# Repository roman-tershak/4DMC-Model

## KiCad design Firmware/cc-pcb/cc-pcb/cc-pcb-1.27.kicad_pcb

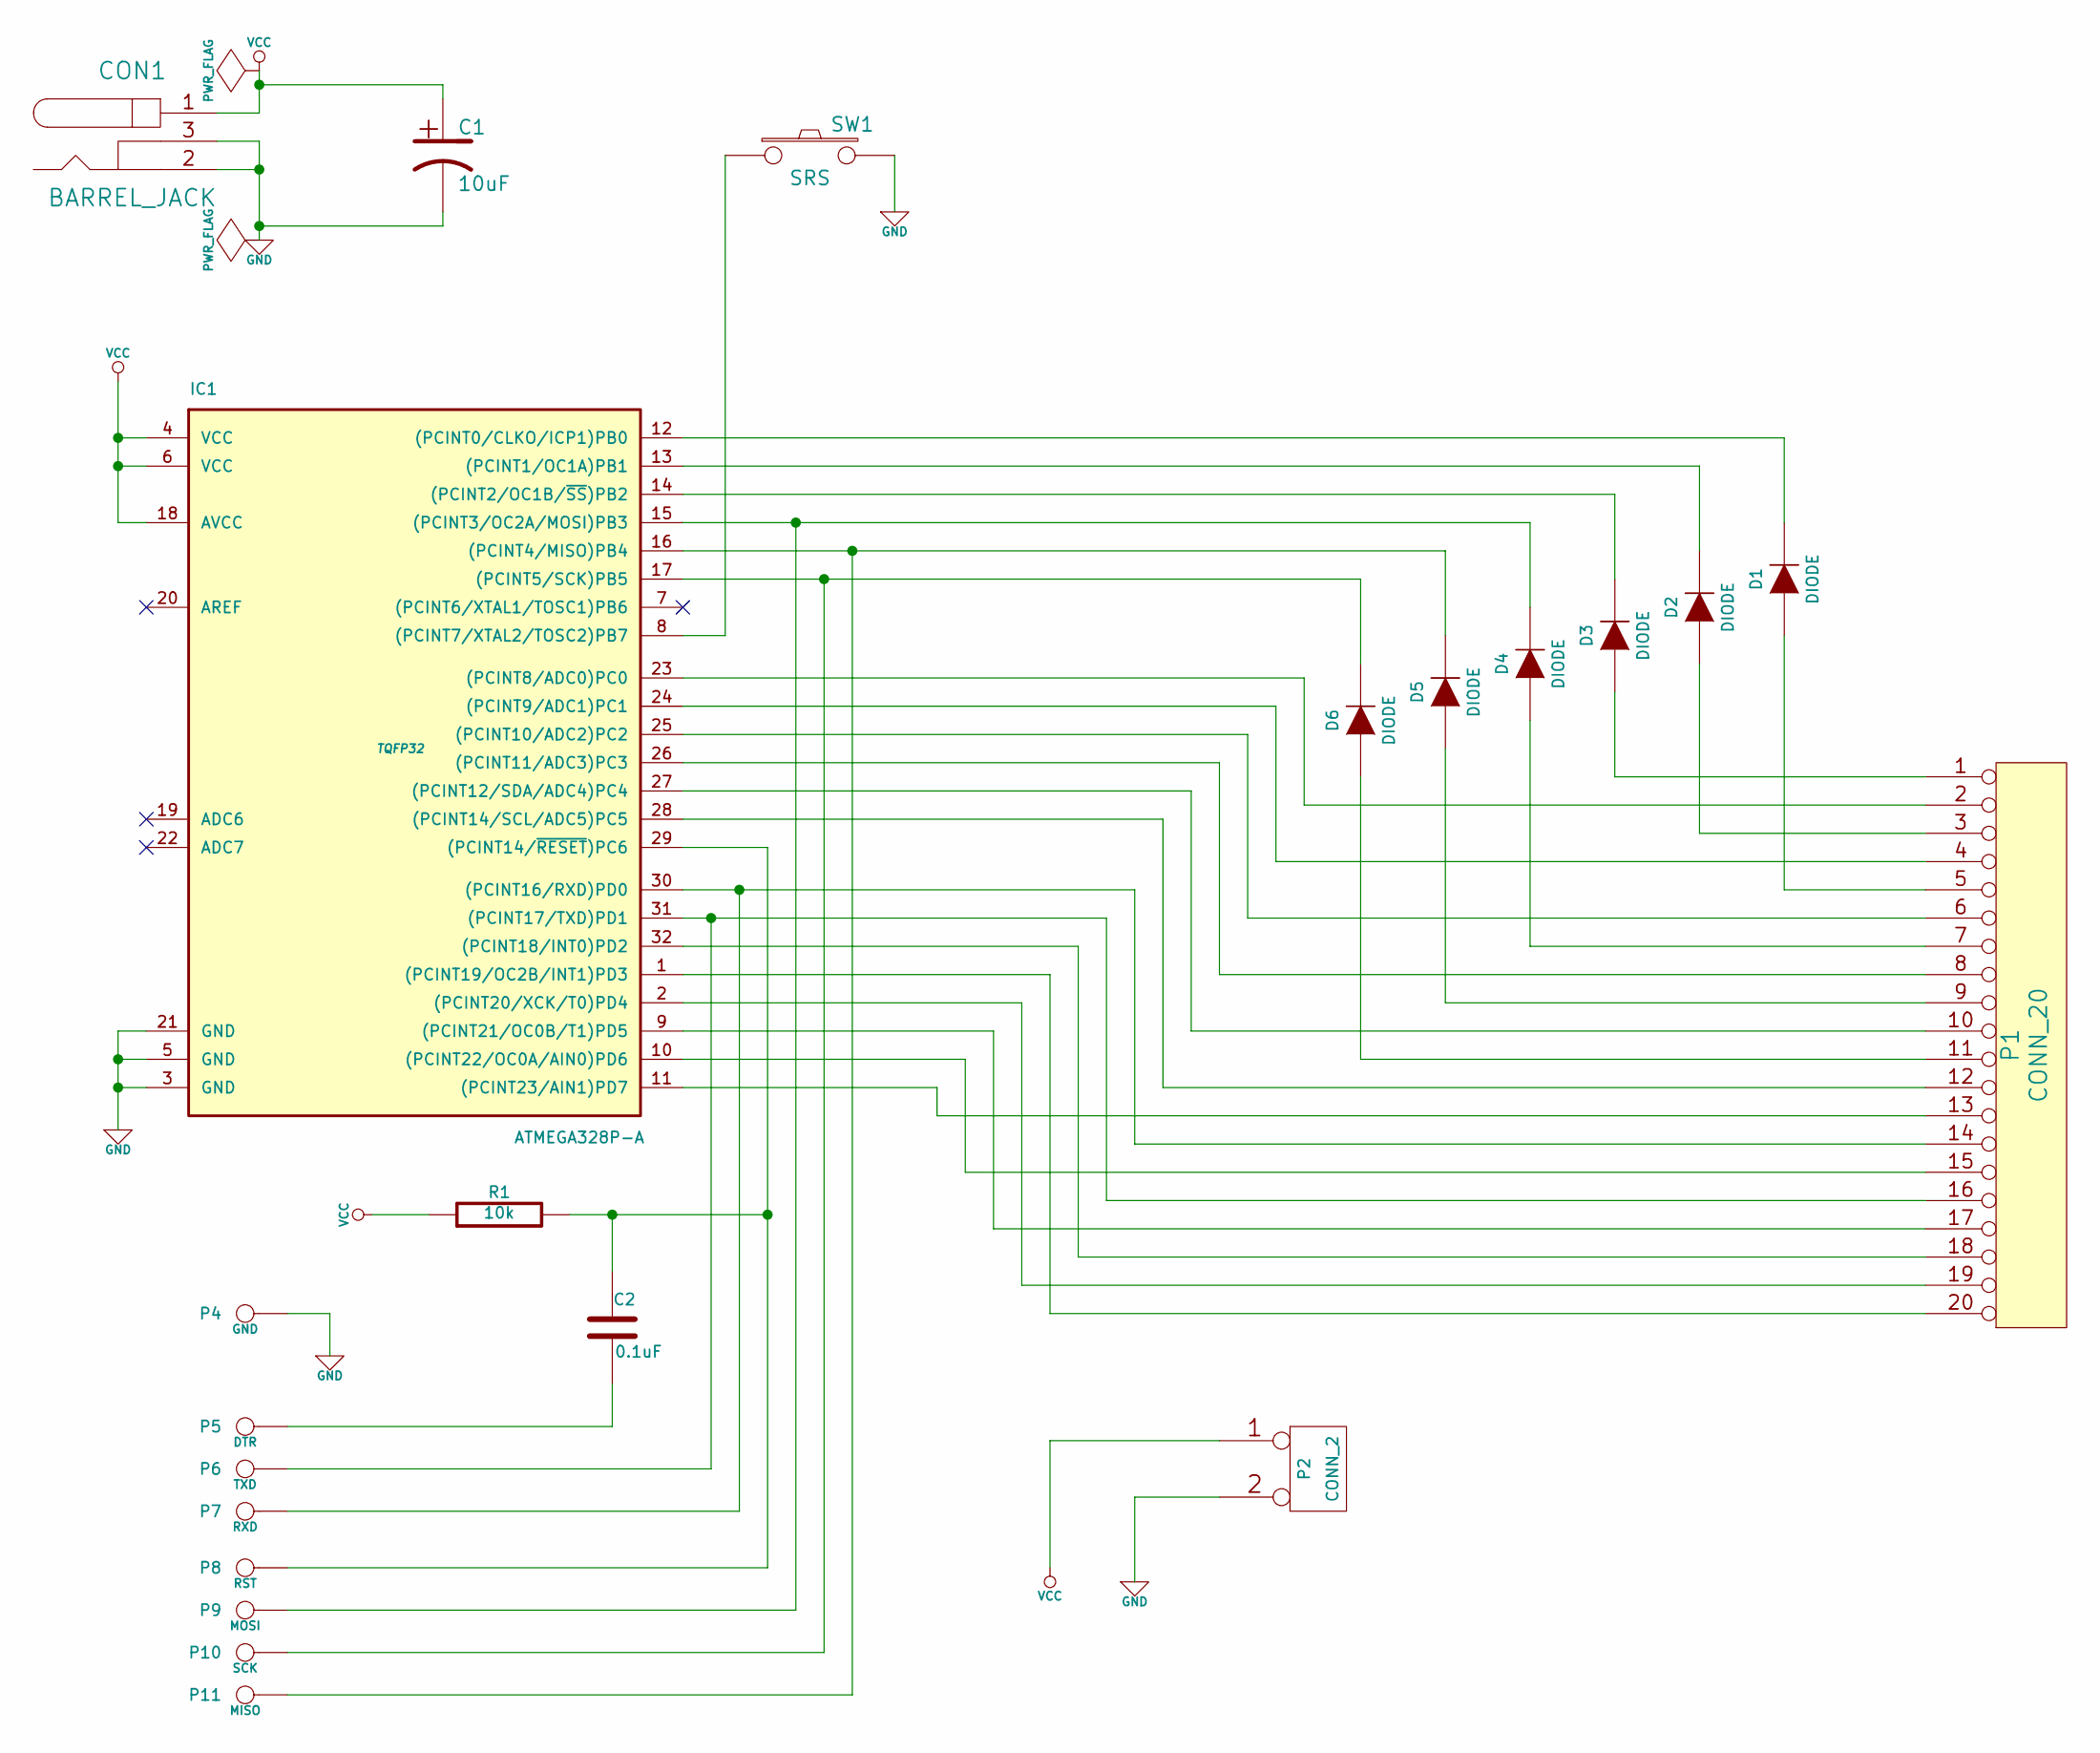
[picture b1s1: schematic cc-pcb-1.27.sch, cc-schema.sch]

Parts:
C1: 10uF
C2: 0.1uF
CON1: BARREL_JACK
D1, D2, D3, D4, D5, D6: DIODE
IC1: ATMEGA328P-A; TQFP32
P1: CONN_20
P2: CONN_2
P4: GND
P5: DTR
P6: TXD
P7: RXD
P8: RST
P9: MOSI
P10: SCK
P11: MISO
R1: 10k
SW1: SRS

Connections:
GND: C1.2, CON1.2, CON1.3, IC1.3 (GND), IC1.5 (GND), IC1.21 (GND), P2.2 (PM), P4.1, SW1.2
unnamed: IC1.28 ((PCINT14/SCL/ADC5)PC5), P1.12
unnamed: IC1.8 ((PCINT7/XTAL2/TOSC2)PB7), SW1.1
unnamed: IC1.9 ((PCINT21/OC0B/T1)PD5), P1.17
unnamed: D5.1 (A), P1.9
unnamed: IC1.26 ((PCINT11/ADC3)PC3), P1.8
unnamed: IC1.27 ((PCINT12/SDA/ADC4)PC4), P1.10
unnamed: D1.1 (A), P1.5
unnamed: D2.1 (A), P1.3
unnamed: D3.1 (A), P1.1
unnamed: IC1.11 ((PCINT23/AIN1)PD7), P1.13
unnamed: IC1.10 ((PCINT22/OC0A/AIN0)PD6), P1.15
unnamed: IC1.32 ((PCINT18/INT0)PD2), P1.18
unnamed: D1.2 (K), IC1.12 ((PCINT0/CLKO/ICP1)PB0)
unnamed: D2.2 (K), IC1.13 ((PCINT1/OC1A)PB1)
unnamed: D3.2 (K), IC1.14 ((PCINT2/OC1B/~SS~)PB2)
unnamed: IC1.31 ((PCINT17/TXD)PD1), P1.16, P6.1
unnamed: IC1.1 ((PCINT19/OC2B/INT1)PD3), P1.20
unnamed: IC1.2 ((PCINT20/XCK/T0)PD4), P1.19
unnamed: C2.2, P5.1
unnamed: IC1.30 ((PCINT16/RXD)PD0), P1.14, P7.1
unnamed: C2.1, IC1.29 ((PCINT14/~RESET~)PC6), P8.1, R1.2
unnamed: D5.2 (K), IC1.16 ((PCINT4/MISO)PB4), P11.1
unnamed: D6.2 (K), IC1.17 ((PCINT5/SCK)PB5), P10.1
unnamed: D4.2 (K), IC1.15 ((PCINT3/OC2A/MOSI)PB3), P9.1
unnamed: D6.1 (A), P1.11
unnamed: D4.1 (A), P1.7
unnamed: IC1.23 ((PCINT8/ADC0)PC0), P1.2
unnamed: IC1.24 ((PCINT9/ADC1)PC1), P1.4
unnamed: IC1.25 ((PCINT10/ADC2)PC2), P1.6
VCC: C1.1, CON1.1, IC1.4 (VCC), IC1.6 (VCC), IC1.18 (AVCC), P2.1, R1.1

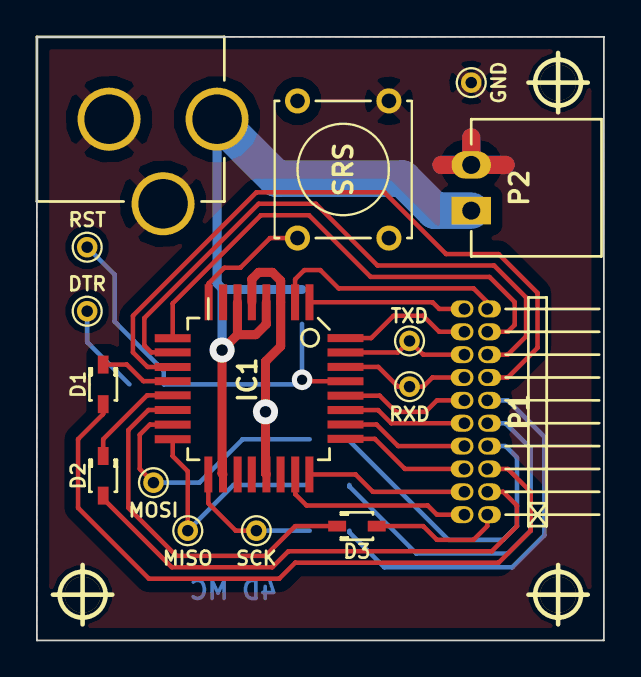
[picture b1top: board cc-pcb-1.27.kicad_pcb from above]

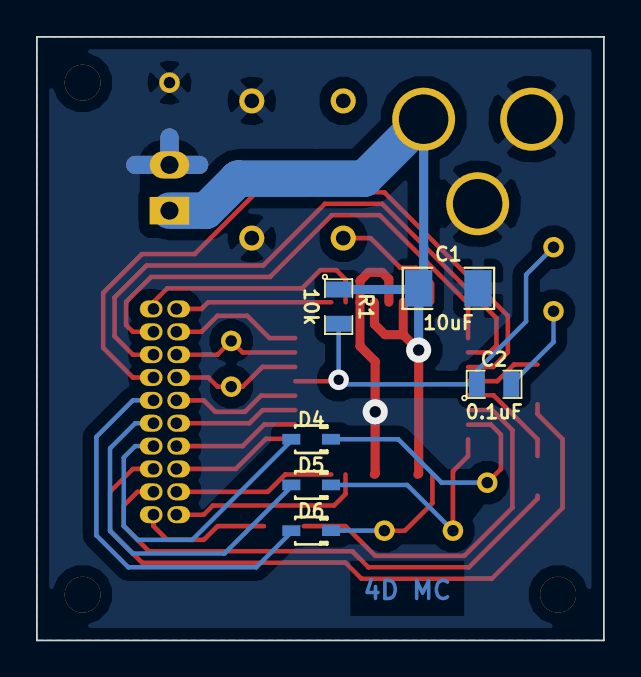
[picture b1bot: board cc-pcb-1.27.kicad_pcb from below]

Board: 2 copper layers, 31.5 x 33.5 mm, 25 parts (6 on the bottom side), 31 nets.

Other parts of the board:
H1, H2, H3: hole_2mm

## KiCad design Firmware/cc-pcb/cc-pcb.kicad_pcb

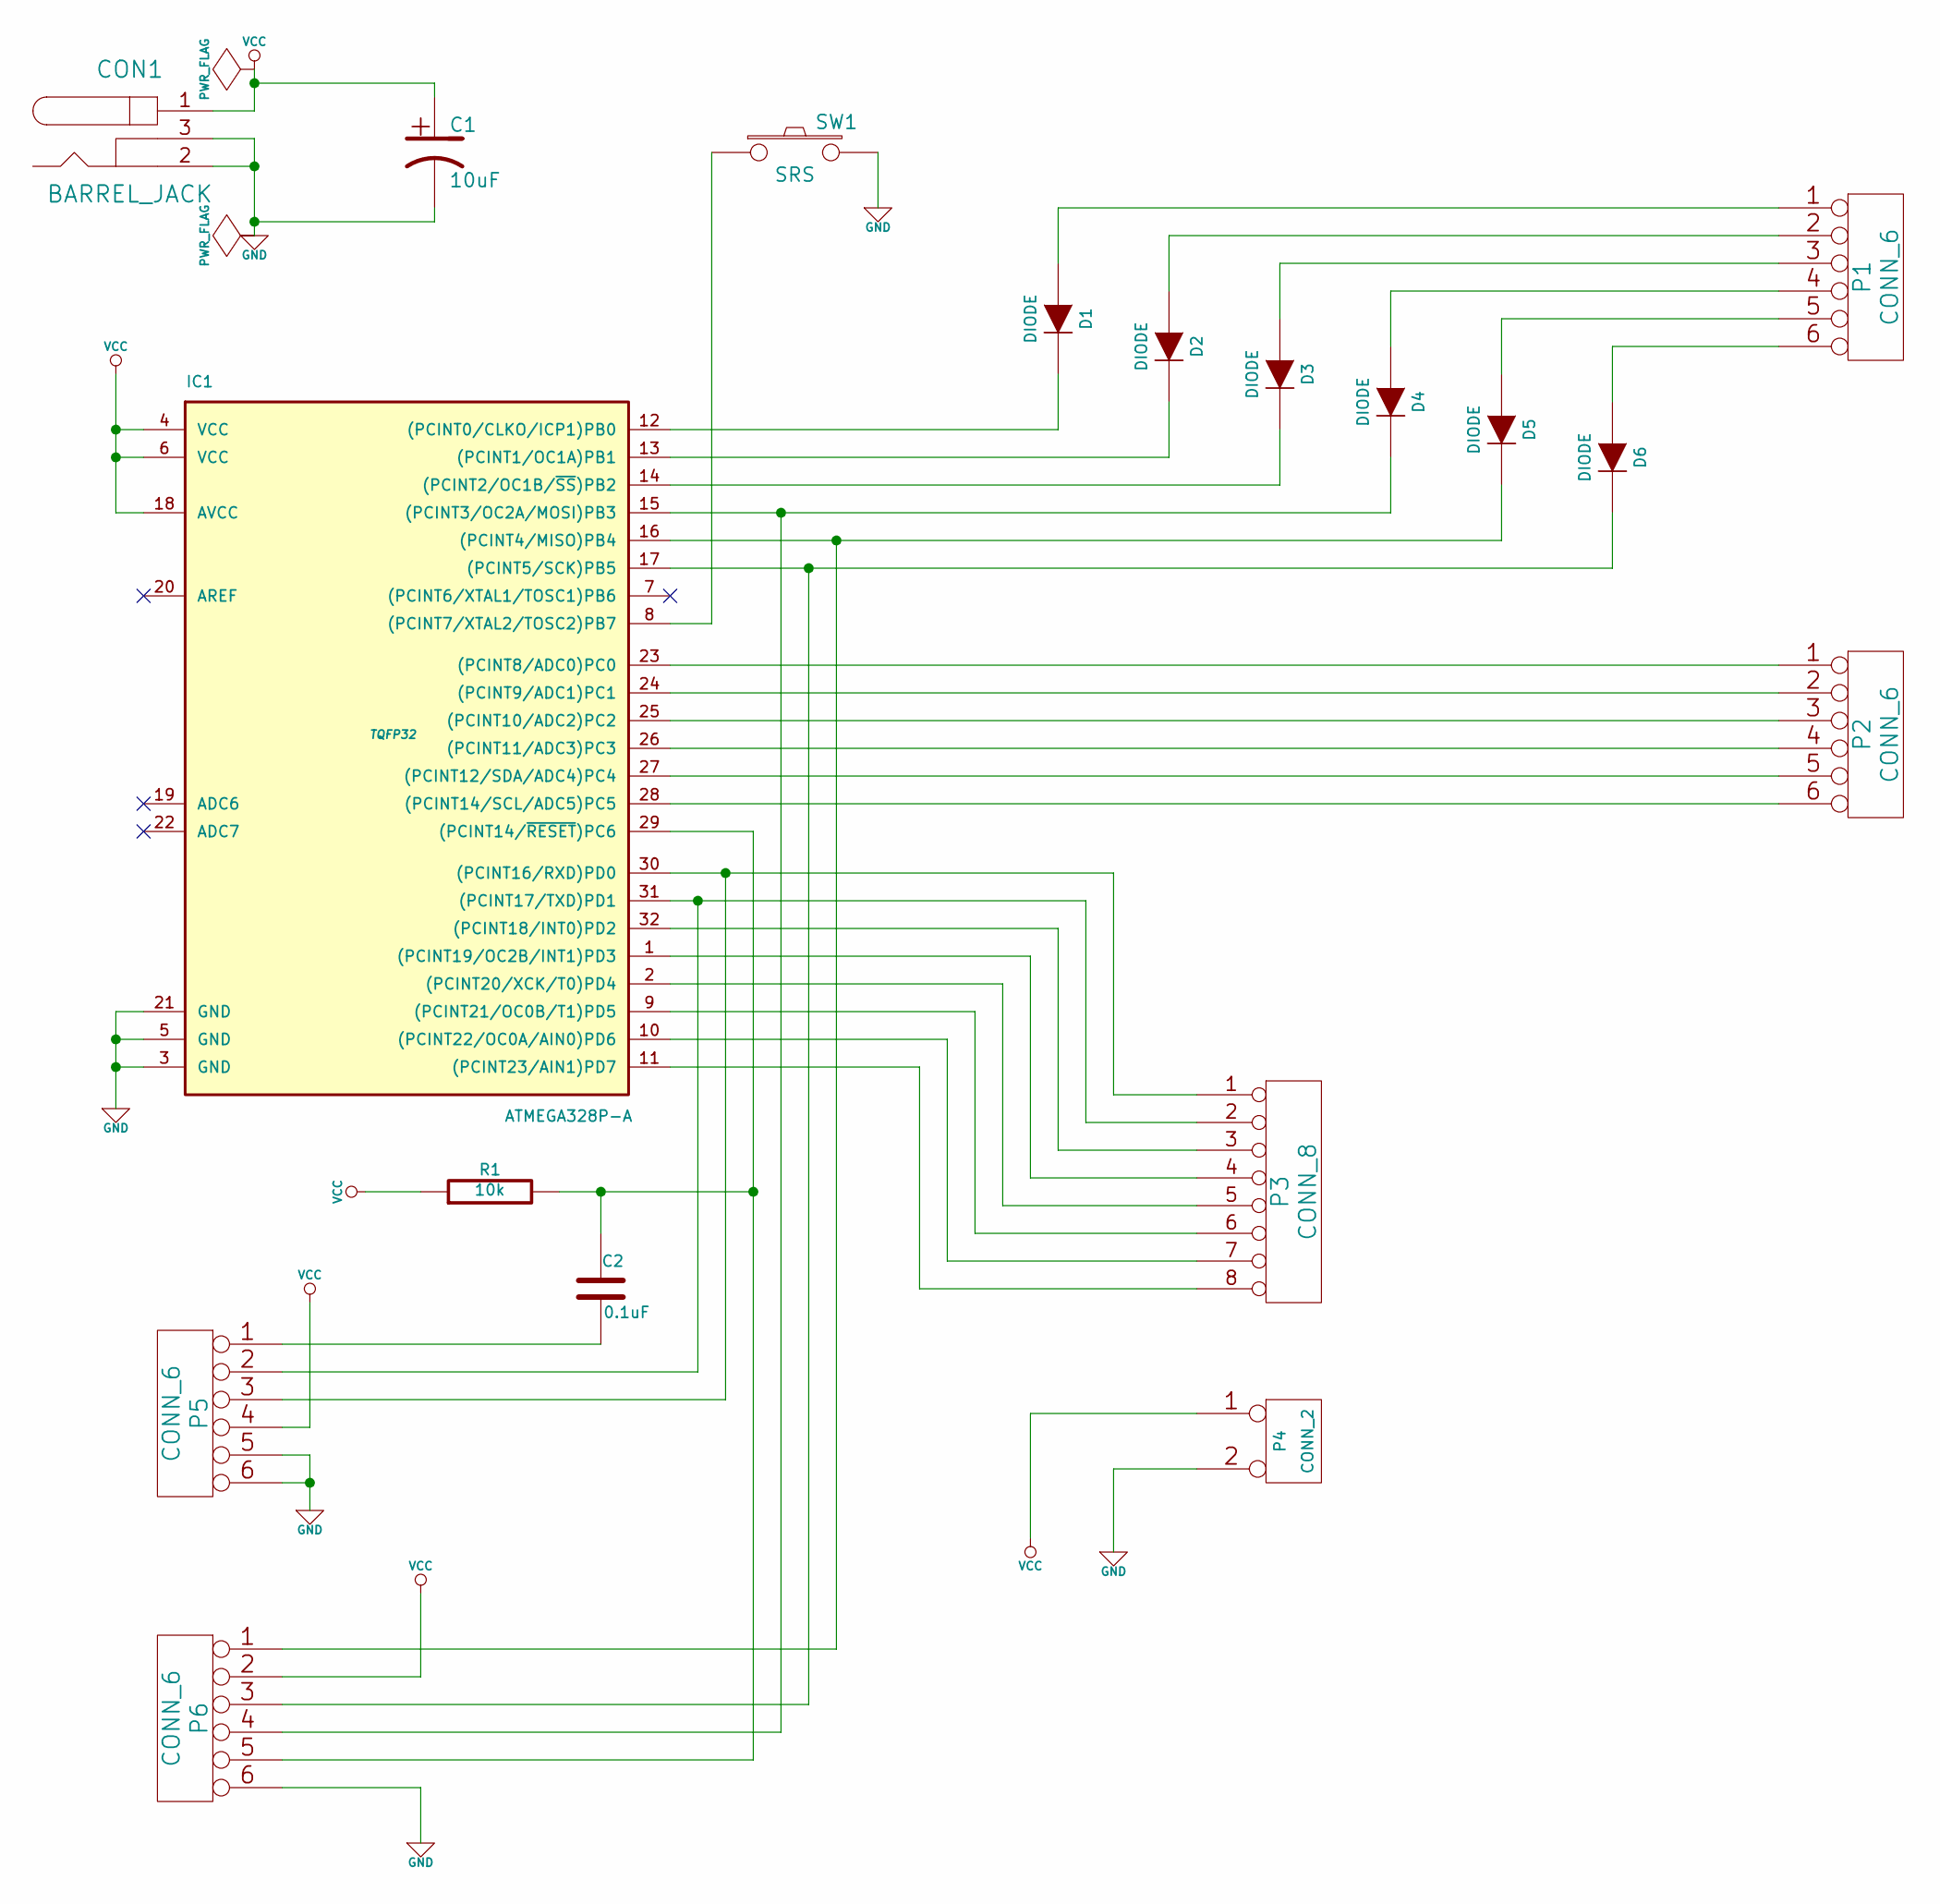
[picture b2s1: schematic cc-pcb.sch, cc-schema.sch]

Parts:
C1: 10uF
C2: 0.1uF
CON1: BARREL_JACK
D1, D2, D3, D4, D5, D6: DIODE
IC1: ATMEGA328P-A; TQFP32
P1, P2, P5, P6: CONN_6
P3: CONN_8
P4: CONN_2
R1: 10k
SW1: SRS

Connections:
GND: C1.2, CON1.2, CON1.3, IC1.3 (GND), IC1.5 (GND), IC1.21 (GND), P4.2 (PM), P5.5, P5.6, P6.6, SW1.2
unnamed: IC1.32 ((PCINT18/INT0)PD2), P3.3
unnamed: IC1.31 ((PCINT17/TXD)PD1), P3.2, P5.2
unnamed: C2.1, IC1.29 ((PCINT14/~RESET~)PC6), P6.5, R1.2
unnamed: C2.2, P5.1
unnamed: IC1.28 ((PCINT14/SCL/ADC5)PC5), P2.6
unnamed: D6.2 (K), IC1.17 ((PCINT5/SCK)PB5), P6.3
unnamed: D5.2 (K), IC1.16 ((PCINT4/MISO)PB4), P6.1
unnamed: D4.2 (K), IC1.15 ((PCINT3/OC2A/MOSI)PB3), P6.4
unnamed: D3.2 (K), IC1.14 ((PCINT2/OC1B/~SS~)PB2)
unnamed: D2.2 (K), IC1.13 ((PCINT1/OC1A)PB1)
unnamed: D1.2 (K), IC1.12 ((PCINT0/CLKO/ICP1)PB0)
unnamed: IC1.11 ((PCINT23/AIN1)PD7), P3.8
unnamed: IC1.10 ((PCINT22/OC0A/AIN0)PD6), P3.7
unnamed: IC1.9 ((PCINT21/OC0B/T1)PD5), P3.6
unnamed: IC1.2 ((PCINT20/XCK/T0)PD4), P3.5
unnamed: IC1.1 ((PCINT19/OC2B/INT1)PD3), P3.4
unnamed: IC1.27 ((PCINT12/SDA/ADC4)PC4), P2.5
unnamed: IC1.26 ((PCINT11/ADC3)PC3), P2.4
unnamed: IC1.25 ((PCINT10/ADC2)PC2), P2.3
unnamed: IC1.24 ((PCINT9/ADC1)PC1), P2.2
unnamed: IC1.23 ((PCINT8/ADC0)PC0), P2.1
unnamed: IC1.30 ((PCINT16/RXD)PD0), P3.1, P5.3
unnamed: IC1.8 ((PCINT7/XTAL2/TOSC2)PB7), SW1.1
unnamed: D1.1 (A), P1.1
unnamed: D6.1 (A), P1.6
unnamed: D5.1 (A), P1.5
unnamed: D4.1 (A), P1.4
unnamed: D3.1 (A), P1.3
unnamed: D2.1 (A), P1.2
VCC: C1.1, CON1.1, IC1.4 (VCC), IC1.6 (VCC), IC1.18 (AVCC), P4.1, P5.4, P6.2, R1.1

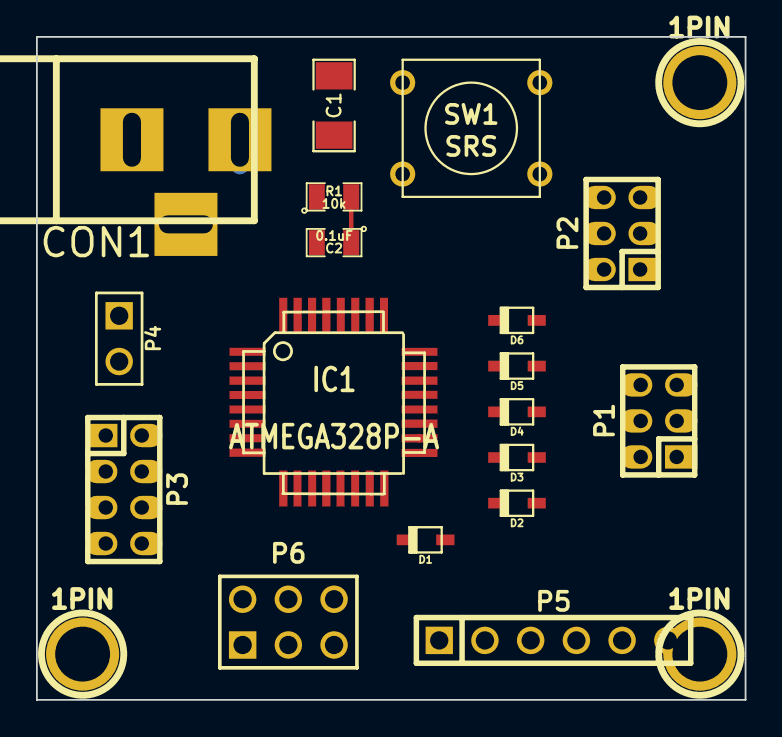
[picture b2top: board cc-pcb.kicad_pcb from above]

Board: 2 copper layers, 39.4 x 36.8 mm, 21 parts (0 on the bottom side), 31 nets.

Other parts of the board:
1PIN, 1PIN#2, 1PIN#3: P***; 1pin

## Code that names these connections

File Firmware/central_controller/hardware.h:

#ifndef H_HARDWARE
#define H_HARDWARE

// The Internal Calibrated RC Oscillator is used. This allows to increase a number of pins
// that can be used as IO pins, as well as to reduce a number of electronic parties.
#undef F_CPU
#define F_CPU 8000000

#include <avr/io.h>
#include <avr/interrupt.h>
#include "common.h"

/* Macros */
#define set_bit(REG, BIT) ((REG) |= _BV(BIT))
#define unset_bit(REG, BIT) ((REG) &= ~_BV(BIT))

#define set_bit_mask(REG, BIT_MASK) ((REG) |= (BIT_MASK))
#define unset_bit_mask(REG, BIT_MASK) ((REG) &= ~(BIT_MASK))

#define set_pin(type) (type ## _PORT |= type ## _MASK)
#define res_pin(type) (type ## _PORT &= ~type ## _MASK)

#define read_pin(type) (type ## _PIN & type ## _MASK)
#define read_pins(type) (type ## _PIN & type ## _MASK)

#define dir_out(type) (type ## _DDR |= type ## _MASK)
#define dir_in(type) (type ## _DDR &= ~type ## _MASK)

/* Pin Definitions */
#ifdef USART_DEBUG
// For debug purposes, should not be used in prod
#define RX_PORT PORTD
#define RX_DDR DDRD
#define RX_MASK _BV(PORTD0)

#define TX_PORT PORTD
#define TX_DDR DDRD
#define TX_MASK _BV(PORTD1)
#endif


// Switches output ports. They enable a side switches scan in the switches matrix
#define SPA_PORT PORTB
#define SPA_DDR DDRB
#define SPA_MASK _BV(PORTB0)  // B0

#define SPB_PORT PORTB
#define SPB_DDR DDRB
#define SPB_MASK _BV(PORTB1)  // B1

#define SPC_PORT PORTB
#define SPC_DDR DDRB
#define SPC_MASK _BV(PORTB2)  // B2

#define SPD_PORT PORTB
#define SPD_DDR DDRB
#define SPD_MASK _BV(PORTB3)  // B3

#define SPE_PORT PORTB
#define SPE_DDR DDRB
#define SPE_MASK _BV(PORTB4)  // B4

#define SPF_PORT PORTB
#define SPF_DDR DDRB
#define SPF_MASK _BV(PORTB5)  // B5

#define SPG_PORT PORTD
#define SPG_DDR DDRD
#define SPG_MASK _BV(PORTD7)  // D7


// Switches input ports. They read a side switches states in the switches matrix
#define SI0_PIN PINC
#define SI0_PORT PORTC
#define SI0_DDR DDRC
#define SI0_MASK _BV(PORTC0)  // C0, XL

#define SI1_PIN PINC
#define SI1_PORT PORTC
#define SI1_DDR DDRC
#define SI1_MASK _BV(PORTC1)  // C1, XR

#define SI2_PIN PINC
#define SI2_PORT PORTC
#define SI2_DDR DDRC
#define SI2_MASK _BV(PORTC2)  // C2, YL

#define SI3_PIN PINC
#define SI3_PORT PORTC
#define SI3_DDR DDRC
#define SI3_MASK _BV(PORTC3)  // C3, YR

#define SI4_PIN PINC
#define SI4_PORT PORTC
#define SI4_DDR DDRC
#define SI4_MASK _BV(PORTC4)  // C4, ZL

#define SI5_PIN PINC
#define SI5_PORT PORTC
#define SI5_DDR DDRC
#define SI5_MASK _BV(PORTC5)  // C5, ZR

#define SI_PIN PINC
#define SI_MASK (SI0_MASK | SI1_MASK | SI2_MASK | SI3_MASK | SI4_MASK | SI5_MASK)


// Software Reset input pin
#define SRS_PIN PINB
#define SRS_PORT PORTB
#define SRS_DDR DDRB
#define SRS_MASK _BV(PORTB7)  // B7


// Color control output pin. It sends control sequences of bytes to side LED's
#define LED_COLOR_PORT PORTD
#define LED_COLOR_DDR DDRD
#define LED_COLOR_MASK _BV(PORTD2)
#define LED_COLOR_PIN PORTD2

// PORT D pins.
#define PD0_PORT PORTD
#define PD0_DDR DDRD
#define PD0_MASK _BV(PORTD0)
#define PD0_PIN PORTD0

#define PD1_PORT PORTD
#define PD1_DDR DDRD
#define PD1_MASK _BV(PORTD1)
#define PD1_PIN PORTD1

// #define PD2_PORT PORTD
// #define PD2_DDR DDRD
// #define PD2_MASK _BV(PORTD2)
// #define PD2_PIN PORTD2

#define PD3_PORT PORTD
#define PD3_DDR DDRD
#define PD3_MASK _BV(PORTD3)
#define PD3_PIN PORTD3

#define PD4_PORT PORTD
#define PD4_DDR DDRD
#define PD4_MASK _BV(PORTD4)
#define PD4_PIN PORTD4

#define PD5_PORT PORTD
#define PD5_DDR DDRD
#define PD5_MASK _BV(PORTD5)
#define PD5_PIN PORTD5

#define PD6_PORT PORTD
#define PD6_DDR DDRD
#define PD6_MASK _BV(PORTD6)
#define PD6_PIN PORTD6

#define PD_PORT PORTD
#define PD_DDR DDRD
#define PD_MASK (PD0_MASK | PD1_MASK | PD3_MASK | PD4_MASK | PD5_MASK | PD6_MASK)
// #define PD_MASK (PD0_MASK | PD1_MASK | PD2_MASK | PD3_MASK | PD4_MASK | PD5_MASK | PD6_MASK)

/* Enable/disable interrupts */
#define ENABLE_GLOBAL_INTERRUPTS()  sei()
#define DISABLE_GLOBAL_INTERRUPTS()  cli()


#ifdef __cplusplus
 extern "C" {
#endif

/* Hardware Functions */
void init_ports(void);
void init_timer1(void);


#ifdef USART_DEBUG
// For debug purposes only

#define USART_TRANSMIT_BYTE(data) USART_transmit(data)
#define USART_TRANSMIT_WORD(data) USART_transmit_16(data)

void USART_init(uint16_t ubrr);
void USART_transmit(uint8_t data);
void USART_transmit_16(uint16_t data);
uint8_t USART_receive(void);

void USART_transmit_buff(uint8_t *buff, uint8_t len);

#else

#define USART_TRANSMIT_BYTE(data)
#define USART_TRANSMIT_WORD(data)

#endif	// End of ifdef USART_DEBUG

#ifdef __cplusplus
}
#endif 

#endif

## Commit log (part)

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2014-11-27 working on join
2014-11-28 working on cronstain
2015-03-01 working on nonmuvable version
2015-03-03 finalizing general geometry
2015-03-05 normalized scales
2015-03-09 tuned sizes and proportions
2015-03-09 enlarging armature
2015-03-11 small change
2015-03-17 started work on samples
2015-03-18 working on samples
2015-03-26 working on samples 1mm
2015-03-26 added more bright colors
2015-03-30 working on samples 1mm+
2015-04-03 working on samples++
2015-04-14 correcting armature
2015-04-14 working on armature
2015-04-15 made curve corne thicker
2015-04-19 working on FE corner parts
2015-04-24 working on corner parts
2015-04-26 enlarging all parts
2015-04-27 enlarging all parts, making central part more spherical
2015-04-29 working on ex central part
2015-05-04 reworking construction for inside-out
2015-05-10 enlarging cubies
2015-05-13 working with curves
2015-05-16 working on curves
2015-06-01 working on the side curve
2015-06-01 working on the corner curve
2015-06-01 enlarging model
2015-06-01 other corrections
2015-06-02 added spikes for the side face
2015-06-03 moving side faces farther
2015-06-03 shaping form
2015-06-04 adding lengths edges
2015-06-05 enlarging extra side edge cubie
2015-06-07 making side face a bit thiner
2015-06-29 working on ext face cubie corner
2015-07-31 working on extra side edge curve holder
2015-08-03 cleaning up extra face corner cubie
2015-08-03 added pazz to extra face corner cubie top face
2015-08-05 separated up and down parts in extra side corner cubie
2015-08-05 finished extra side corner cubie
2015-08-05 working on extra side corner curve
2015-08-05 working on ext face corner curve
2015-08-06 working on ef corner curve
2015-08-09 working on ext face edge curve
2015-08-10 working on ef edge curve
2015-08-11 working on ef curve edge
2015-08-12 finished working on ef edge curve, corner end
2015-08-13 working on ef edge cubie
2015-08-14 working on ef edge corner
2015-08-23 fixing 3dprint issues in ef edge curve
2015-08-23 working on ef corne cubie
2015-08-24 working on side face
2015-08-25 working on fs
2015-08-27 working on sf
2015-08-27 working on se
2015-09-01 working onsf, internal side
2015-09-02 finished rounding edges on sf
2015-09-02 rounding edges on sf
2015-09-06 working on sf stinkt
2015-09-08 working on ef curve corner-sf connection
2015-09-09 working on sf+curve corner
2015-09-10 working on sf curve corner connection
2015-09-13 working on sf-curve corner connector
2015-09-19 working on ef-curve corner connector
2015-09-24 working on ef-curve edge connector
2015-09-28 working on ef edge cubie - curve connector
2015-09-30 working on ef corner cubie - curve connector
2015-10-07 made spikes more wide in the outer end
2015-10-07 added LED spike to ef corner cubie
2015-10-12 working on ef edge - curve connector
2015-10-13 reworking ef corner cubie - edge curve connector
2015-10-14 reworking curves connectors
2015-10-19 working on corner curve
2015-10-23 working on corner curve simple conn
2015-11-02 working on edge curve
2015-11-08 reworking curves
2015-11-11 finalizing curve geometry for SimConOut
2015-11-18 working on corner curve FS connector
2015-11-20 working on curve corner - fs connector
2015-11-20 working on corner curve - fs connector
2015-11-21 working on corner curve - ef corner connector
2015-11-23 working on connector
2015-11-23 working on corner curves
2015-11-25 making corner curve wider
2015-11-26 working on sf - corner curve connector
2015-11-27 working on sf - making connectors wider
2015-11-29 working on ef
2015-11-30 working on ef, corner cubie
2015-12-09 made ef corner cubie larger
2015-12-10 working on corner cubie - curve corner connector
2015-12-11 working on ef edge cubie - edge curve connector
2015-12-14 working on ef corner cubie
2015-12-16 working on ef corner cubie - side curve
2015-12-22 created print model for ef corner cubie
2015-12-23 created a couple of print models
2015-12-24 before merging print models into one
2015-12-24 created print model
2015-12-25 changed print model
2015-12-28 created print model, sent for print
2015-12-29 started working on FS
2016-02-16 made corner curve wider
2016-02-27 created initial geometry of corner item for 4d 2mc
2016-02-28 initial version of corner items and the cube
2016-02-28 other versions of corner items and the cube
2016-03-08 defining form and size
2016-03-09 finalized size
2016-03-12 working on frame and cap
2016-03-28 trying octahedron
2016-03-30 making frame more triangle
2016-04-02 working on ext shell
2016-04-02 working on the form & size
2016-04-02 finalizing form and geom
2016-04-02 minor changes
2016-04-03 working on cubish form
2016-04-05 working on tetra cap
2016-04-06 working on ext frame of cubish form
2016-04-09 merged frame with vt
2016-04-10 finalizing work on cubish elem
2016-04-23 added external frame
2016-04-24 added frames
2016-04-24 working on frames
2016-04-30 made size smaller, developed side pipe
2016-05-01 working on the ext pipe
2016-05-02 started working on ext pipe
2016-06-12 working on switches
2016-06-13 working on side bar
2016-06-13 a bit
2016-06-14 working on button frame
2016-06-18 working on switch frame and cap
2016-06-19 working on switch frame
2016-06-20 Working on switch cap
2016-06-21 Working on switch
2016-06-28 before merge
2016-06-28 merged switch and ext stick
2016-06-29 working on central switch
2016-06-30 working on the central switch
2016-07-02 making holes wider
2016-07-03 woking on cenral switch
2016-07-06 working on ext stick holder
2016-07-07 working on external stick
2016-08-12 working on upper corner switch cap
2016-08-15 working on ext stick
2016-08-17 merged int and ext shapes of ext stick together
2016-08-17 fixed the merge
2016-08-18 preparing ext stick elements for printing
2016-08-21 making parts complete
2016-08-24 sent to print to 3dprintuk
2016-08-24 working on internal tube
2016-08-27 making middle tube larger
2016-08-30 working on int switch frame
2016-08-30 working on internal switch
2016-09-08 working on int stick
2016-09-08 working on int stick cap
2016-09-09 working on down stick holder
2016-09-10 working on down side stick
2016-09-14 working on the board
2016-09-17 before merging down box with sticks
2016-09-17 down dox with sticks
2016-10-09 III attempt
2016-10-09 made base geometry
2016-10-16 adjusting colors, enabled 8th side
2016-10-22 finilizing base geometry
2016-10-23 made base geometry of cubies
2016-10-24 made frame and cap
2016-10-24 working on cubie cap and led holder
2016-10-25 created 2 cubie caps
2016-10-25 made cubie frame
2016-10-25 finalyzing cubie
2016-10-26 generated cubie frame and cap models
2016-11-06 working on side tube
2016-11-06 working on int tube
2016-11-13 created int and ext tubes geometry
2017-01-09 working on ext tube switches
2017-01-11 sent to printer
2017-01-15 working on board box
2017-01-22 before adding board holders to the board box
2017-01-22 finished board box
2017-02-26 less in 90%
2017-02-26 working on it
2017-03-12 made wire holders bigger
2017-03-12 in the middle of working on ext tube
2017-03-19 developed int tube with switch
2017-03-19 working on ext tube
2017-04-02 working on ext tubes
2017-04-12 working on side down tube
2017-04-15 working on down tube
2017-04-17 working on side tubes & down tube & the box
2017-04-19 working on ext tube lids
2017-04-30 all printables ready
2017-04-30 sent to printer 2.1
2017-04-30 as whole object
2017-05-29 corrected switch cap, box and int tube
2017-05-31 corrections after tests
2017-05-31 corrected frame
2017-05-31 adding latches to the tubes
2017-06-01 made the latches narrower
2017-06-01 added latches to ext tubes
2017-06-01 added latches to side tube
2017-06-02 added latches to side down tubes
2017-06-08 working on fr with led holders
2017-06-08 1st fr w/ led latches
2017-06-26 generated STLs
2017-08-11 Changing FW to 2*2*2*2 configuration
2017-08-11 minor fix
2017-08-15 further changing logic to 2*2 cube
2017-08-16 changing some comments
2017-08-16 added CF sensors
2017-08-20 typo
2017-08-20 added physical-to-logical led conversion
2017-08-22 drew LED cube
2017-08-23 adding LED-to-stickers matrix
2017-08-23 led-to-stickers done
2017-08-27 working on 2*2 logic
2017-08-28 working on sensors
2017-08-29 working on CB switches logic
2017-08-29 reworked faster/slower logic
2017-08-31 working on 2*2 model
2017-09-01 finished, compiles
2017-09-04 minors
2017-09-05 added USART debug code
2017-10-10 Added Pins to Contacts + minors
2017-10-29 merging changes
2017-11-16 Fixing incorrect rotation of CF side
2017-11-16 Made rotation faster, transitioning not so dimmed
2017-12-04 removed transition states
2017-12-05 making final changes
2017-12-05 fixed rotation logic + set double click timeout and interrupts
2017-12-11 fixing incorrect rotation of the external side
2017-12-12 removed side switches structure
2017-12-12 minor
2017-12-12 fixed bugs, changed collors, adjusted ext side rotation
2018-01-01 adjusted orange collor
